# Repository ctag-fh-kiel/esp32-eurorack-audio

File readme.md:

# ESP32 Eurorack Audio Synthesis Module
Hardware for Strämpler

## What it is
Base board (design with KiCad) for using the ESP32 WROVER module in the context of real-time audio applications for eurorack synthesizer setups.

## Errata
CV in 1+2 are -1.5V .. 5.5V

## License
Licensed under CC BY-NC-SA 4.0
https://creativecommons.org/licenses/by-nc-sa/4.0/
(C) Robert Manzke 2019

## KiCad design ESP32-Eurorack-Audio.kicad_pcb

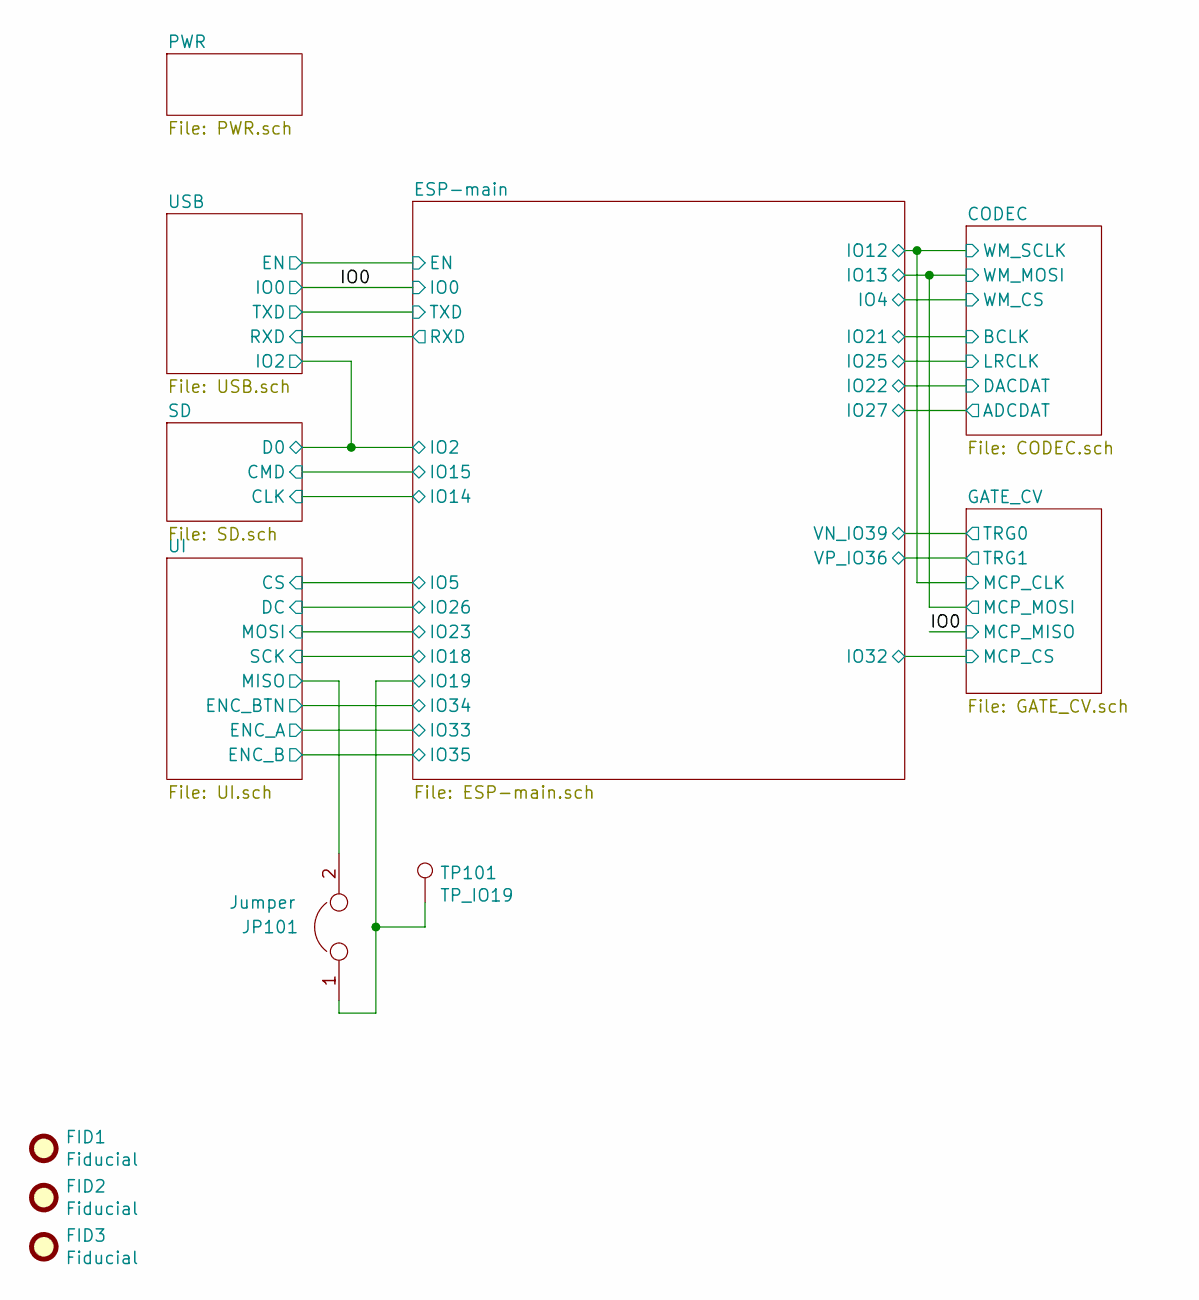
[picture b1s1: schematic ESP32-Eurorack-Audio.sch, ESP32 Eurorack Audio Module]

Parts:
FID1, FID2, FID3: Fiducial; Fiducial_1mm_Mask2mm
JP101: Jumper; SolderJumper-2_P1.3mm_Open_TrianglePad1.0x1.5mm
TP101: TP_IO19; TestPoint_Keystone_5019_Minature

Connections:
/ESP-main/IO19: JP101.1, TP101.1; also elsewhere on the board
/UI/MISO: JP101.2; also elsewhere on the board

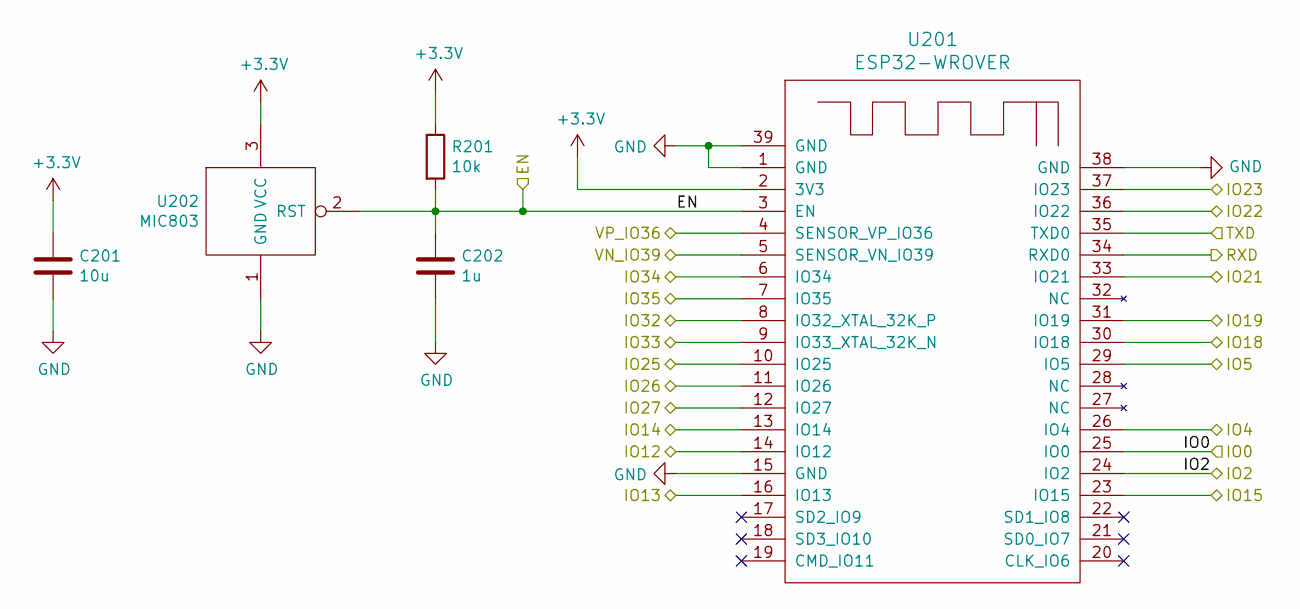
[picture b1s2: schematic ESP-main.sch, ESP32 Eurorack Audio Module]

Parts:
C201: 10u; C_0805_2012Metric
C202: 1u; C_0603_1608Metric
R201: 10k; R_0603_1608Metric
U201: ESP32-WROVER
U202: MIC803; SOT-23

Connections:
/CODEC/ADCDAT: U201.12 (IO27); also elsewhere on the board
/CODEC/BCLK: U201.33 (IO21); also elsewhere on the board
/CODEC/DACDAT: U201.36 (IO22); also elsewhere on the board
/ESP-main/EN: C202.1, R201.2, U201.3 (EN), U202.2 (RST); also elsewhere on the board
/ESP-main/IO4: U201.26 (IO4); also elsewhere on the board
/ESP-main/IO12: U201.14 (IO12); also elsewhere on the board
/ESP-main/IO13: U201.16 (IO13); also elsewhere on the board
/ESP-main/IO18: U201.30 (IO18); also elsewhere on the board
/ESP-main/IO19: U201.31 (IO19); also elsewhere on the board
/ESP-main/IO23: U201.37 (IO23); also elsewhere on the board
/ESP-main/IO25: U201.10 (IO25); also elsewhere on the board
/ESP-main/IO32: U201.8 (IO32_XTAL_32K_P); also elsewhere on the board
/ESP-main/RXD: U201.34 (RXD0); also elsewhere on the board
/ESP-main/TXD: U201.35 (TXD0); also elsewhere on the board
/GATE_CV/TRG0: U201.5 (SENSOR_VN_IO39); also elsewhere on the board
/GATE_CV/TRG1: U201.4 (SENSOR_VP_IO36); also elsewhere on the board
/IO0: U201.25 (IO0); also elsewhere on the board
/SD/CLK: U201.13 (IO14); also elsewhere on the board
/SD/CMD: U201.23 (IO15); also elsewhere on the board
/SD/D0: U201.24 (IO2); also elsewhere on the board
/UI/CS: U201.29 (IO5); also elsewhere on the board
/UI/DC: U201.11 (IO26); also elsewhere on the board
/UI/ENC_A: U201.9 (IO33_XTAL_32K_N); also elsewhere on the board
/UI/ENC_B: U201.7 (IO35); also elsewhere on the board
/UI/ENC_BTN: U201.6 (IO34); also elsewhere on the board
GND: C201.2, C202.2, U201.1 (GND), U201.15 (GND), U201.38 (GND), U201.39 (GND), U202.1 (GND); also elsewhere on the board

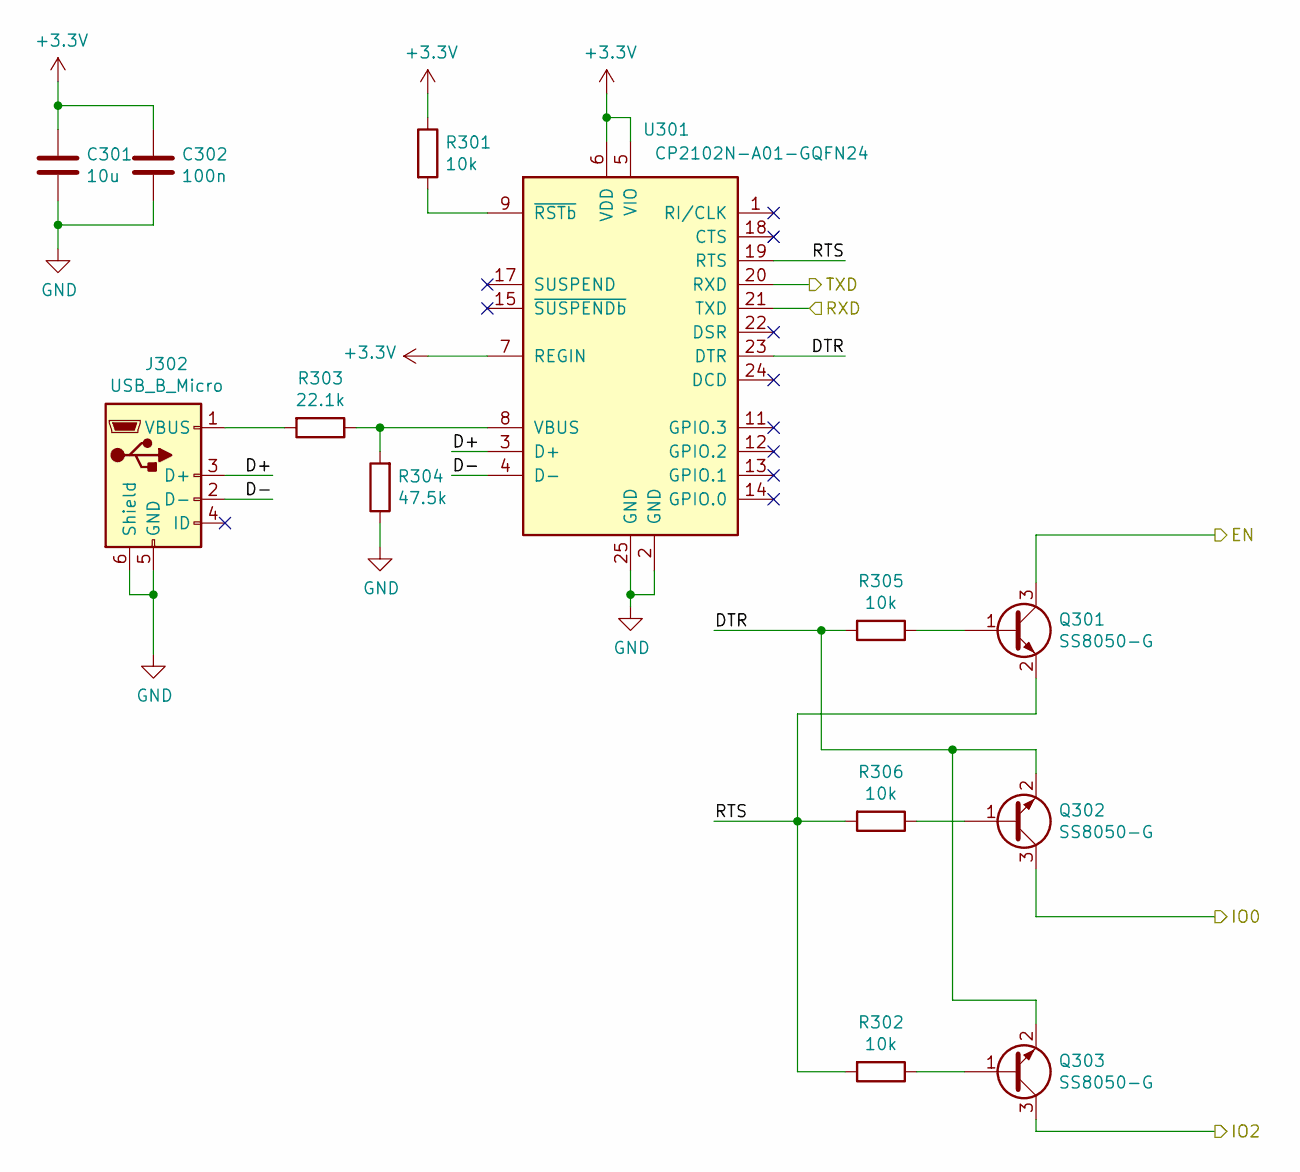
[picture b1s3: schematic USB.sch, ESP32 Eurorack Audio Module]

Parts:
C301: 10u; C_0805_2012Metric
C302: 100n; C_0603_1608Metric
J302: USB_B_Micro; USB_Micro-B_Molex-105017-0001
Q301, Q302, Q303: SS8050-G; SOT-23
R301, R302, R305, R306: 10k; R_0603_1608Metric
R303: 22.1k; R_0603_1608Metric
R304: 47.5k; R_0603_1608Metric
U301: CP2102N-A01-GQFN24; QFN-24-1EP_4x4mm_P0.5mm_EP2.6x2.6mm

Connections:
/ESP-main/EN: Q301.3 (C); also elsewhere on the board
/ESP-main/RXD: U301.21 (TXD); also elsewhere on the board
/ESP-main/TXD: U301.20 (RXD); also elsewhere on the board
/IO0: Q302.3 (C); also elsewhere on the board
/SD/D0: Q303.3 (C); also elsewhere on the board
/USB/D+: J302.3 (D+), U301.3 (D+)
/USB/D-: J302.2 (D-), U301.4 (D-)
/USB/DTR: Q302.2 (E), Q303.2 (E), R305.2, U301.23 (DTR)
/USB/RTS: Q301.2 (E), R302.2, R306.2, U301.19 (RTS)
GND: C301.2, C302.2, J302.5 (GND), J302.6 (Shield), R304.1, U301.2 (GND), U301.25 (GND); also elsewhere on the board
unnamed: J302.1 (VBUS), R303.2
unnamed: Q301.1 (B), R305.1
unnamed: Q302.1 (B), R306.1
unnamed: Q303.1 (B), R302.1
unnamed: R301.2, U301.9 (~RSTb)
unnamed: R303.1, R304.2, U301.8 (VBUS)

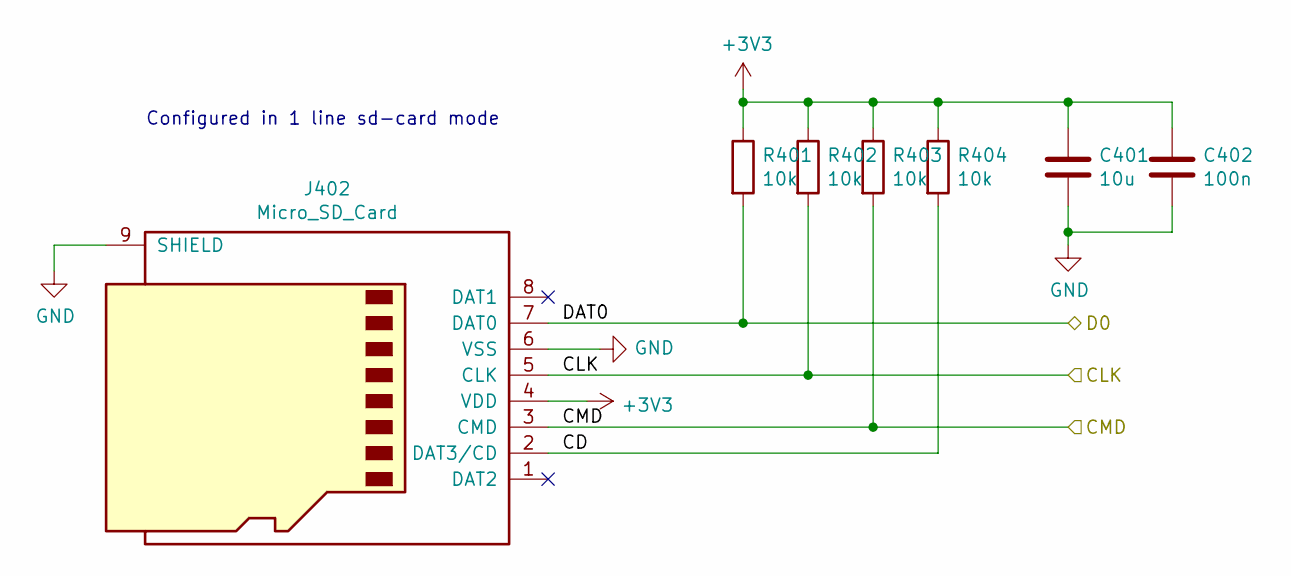
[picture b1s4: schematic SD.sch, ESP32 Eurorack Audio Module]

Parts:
C401: 10u; C_0805_2012Metric
C402: 100n; C_0603_1608Metric
J402: Micro_SD_Card; microSD_HC_Hirose_DM3D-SF
R401, R402, R403, R404: 10k; R_0603_1608Metric

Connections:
/SD/CD: J402.2 (DAT3/CD), R404.2
/SD/CLK: J402.5 (CLK), R402.2; also elsewhere on the board
/SD/CMD: J402.3 (CMD), R403.2; also elsewhere on the board
/SD/D0: J402.7 (DAT0), R401.2; also elsewhere on the board
GND: C401.2, C402.2, J402.6 (VSS), J402.9 (SHIELD); also elsewhere on the board

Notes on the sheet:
Configured in 1 line sd-card mode

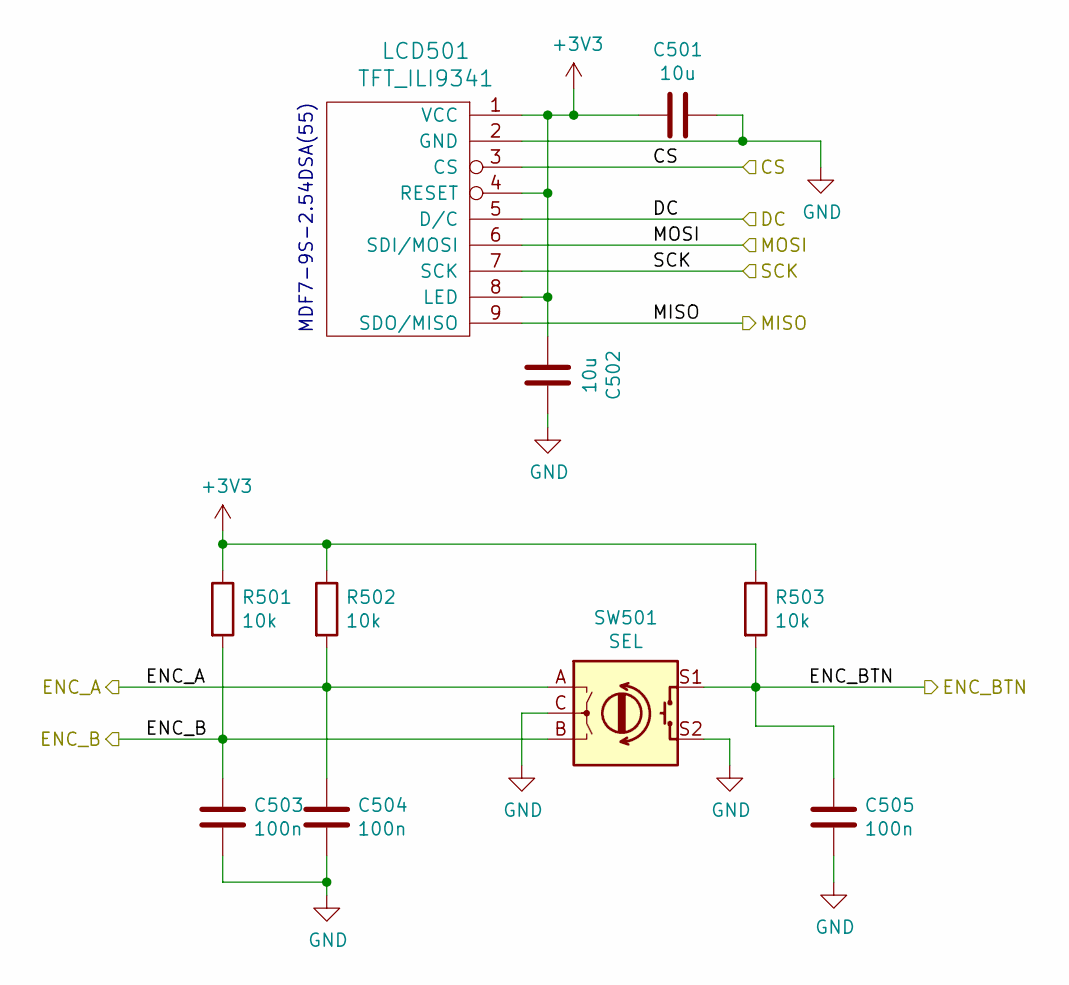
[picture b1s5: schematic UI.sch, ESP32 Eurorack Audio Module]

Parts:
C501, C502: 10u; C_0805_2012Metric
C503, C504, C505: 100n; C_0603_1608Metric
LCD501: TFT_ILI9341; TFT_2.2
R501, R502, R503: 10k; R_0603_1608Metric
SW501: SEL; RotaryEncoder_Alps_EC11E-Switch_Vertical_H20mm

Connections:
/ESP-main/IO18: LCD501.7 (SCK); also elsewhere on the board
/ESP-main/IO23: LCD501.6 (SDI/MOSI); also elsewhere on the board
/UI/CS: LCD501.3 (CS); also elsewhere on the board
/UI/DC: LCD501.5 (D/C); also elsewhere on the board
/UI/ENC_A: C504.2, R502.2, SW501.A; also elsewhere on the board
/UI/ENC_B: C503.2, R501.2, SW501.B; also elsewhere on the board
/UI/ENC_BTN: C505.2, R503.2, SW501.S1; also elsewhere on the board
/UI/MISO: LCD501.9 (SDO/MISO); also elsewhere on the board
GND: C501.1, C502.1, C503.1, C504.1, C505.1, LCD501.2 (GND), SW501.C, SW501.S2; also elsewhere on the board

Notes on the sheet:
MDF7-9S-2.54DSA(55)

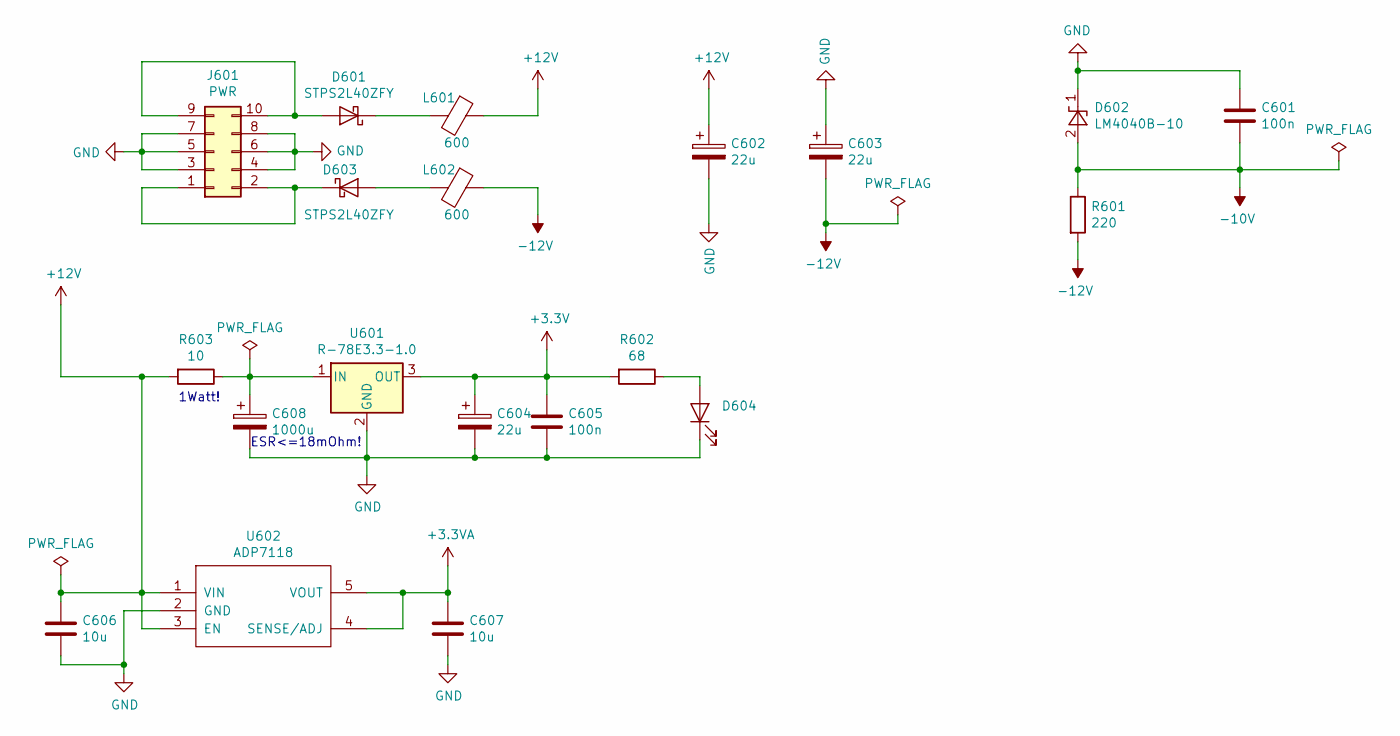
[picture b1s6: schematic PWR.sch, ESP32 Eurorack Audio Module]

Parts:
C601, C605: 100n; C_0603_1608Metric
C602, C603, C604: 22u; CP_EIA-3216-12_Kemet-S
C606: 10u; C_1210_3225Metric
C607: 10u; C_0805_2012Metric
C608: 1000u; CP_Elec_10x12.6
D601, D603: STPS2L40ZFY; D_SOD-123
D602: LM4040B-10; SOT-23
D604: LED_D5.0mm_Clear
J601: PWR; PinHeader_2x05_P2.54mm_Vertical
L601, L602: 600; C_0805_2012Metric
R601: 220; R_0603_1608Metric
R602: 68; R_0805_2012Metric
R603: 10; R_2512_6332Metric
U601: R-78E3.3-1.0; SIP3_11.6x8.5mm
U602: ADP7118; TSOT-23-5

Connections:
+3.3VA: C607.1, U602.4 (SENSE/ADJ), U602.5 (VOUT); also elsewhere on the board
+12V: C602.1, C606.1, L601.1, R603.2, U602.1 (VIN), U602.3 (EN); also elsewhere on the board
-10V: C601.2, D602.2 (A), R601.1; also elsewhere on the board
-12V: C603.2, L602.1, R601.2; also elsewhere on the board
GND: C601.1, C602.2, C603.1, C604.2, C605.2, C606.2, C607.2, C608.2, D602.1 (K), D604.1 (K), J601.3, J601.4, J601.5, J601.6, J601.7, J601.8, U601.2 (GND), U602.2 (GND); also elsewhere on the board
unnamed: C608.1, R603.1, U601.1 (IN)
unnamed: D601.1 (K), L601.2
unnamed: D601.2 (A), J601.9, J601.10
unnamed: D603.1 (K), J601.1, J601.2
unnamed: D603.2 (A), L602.2
unnamed: D604.2 (A), R602.1

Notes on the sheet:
ESR<=18mOhm!
1Watt!

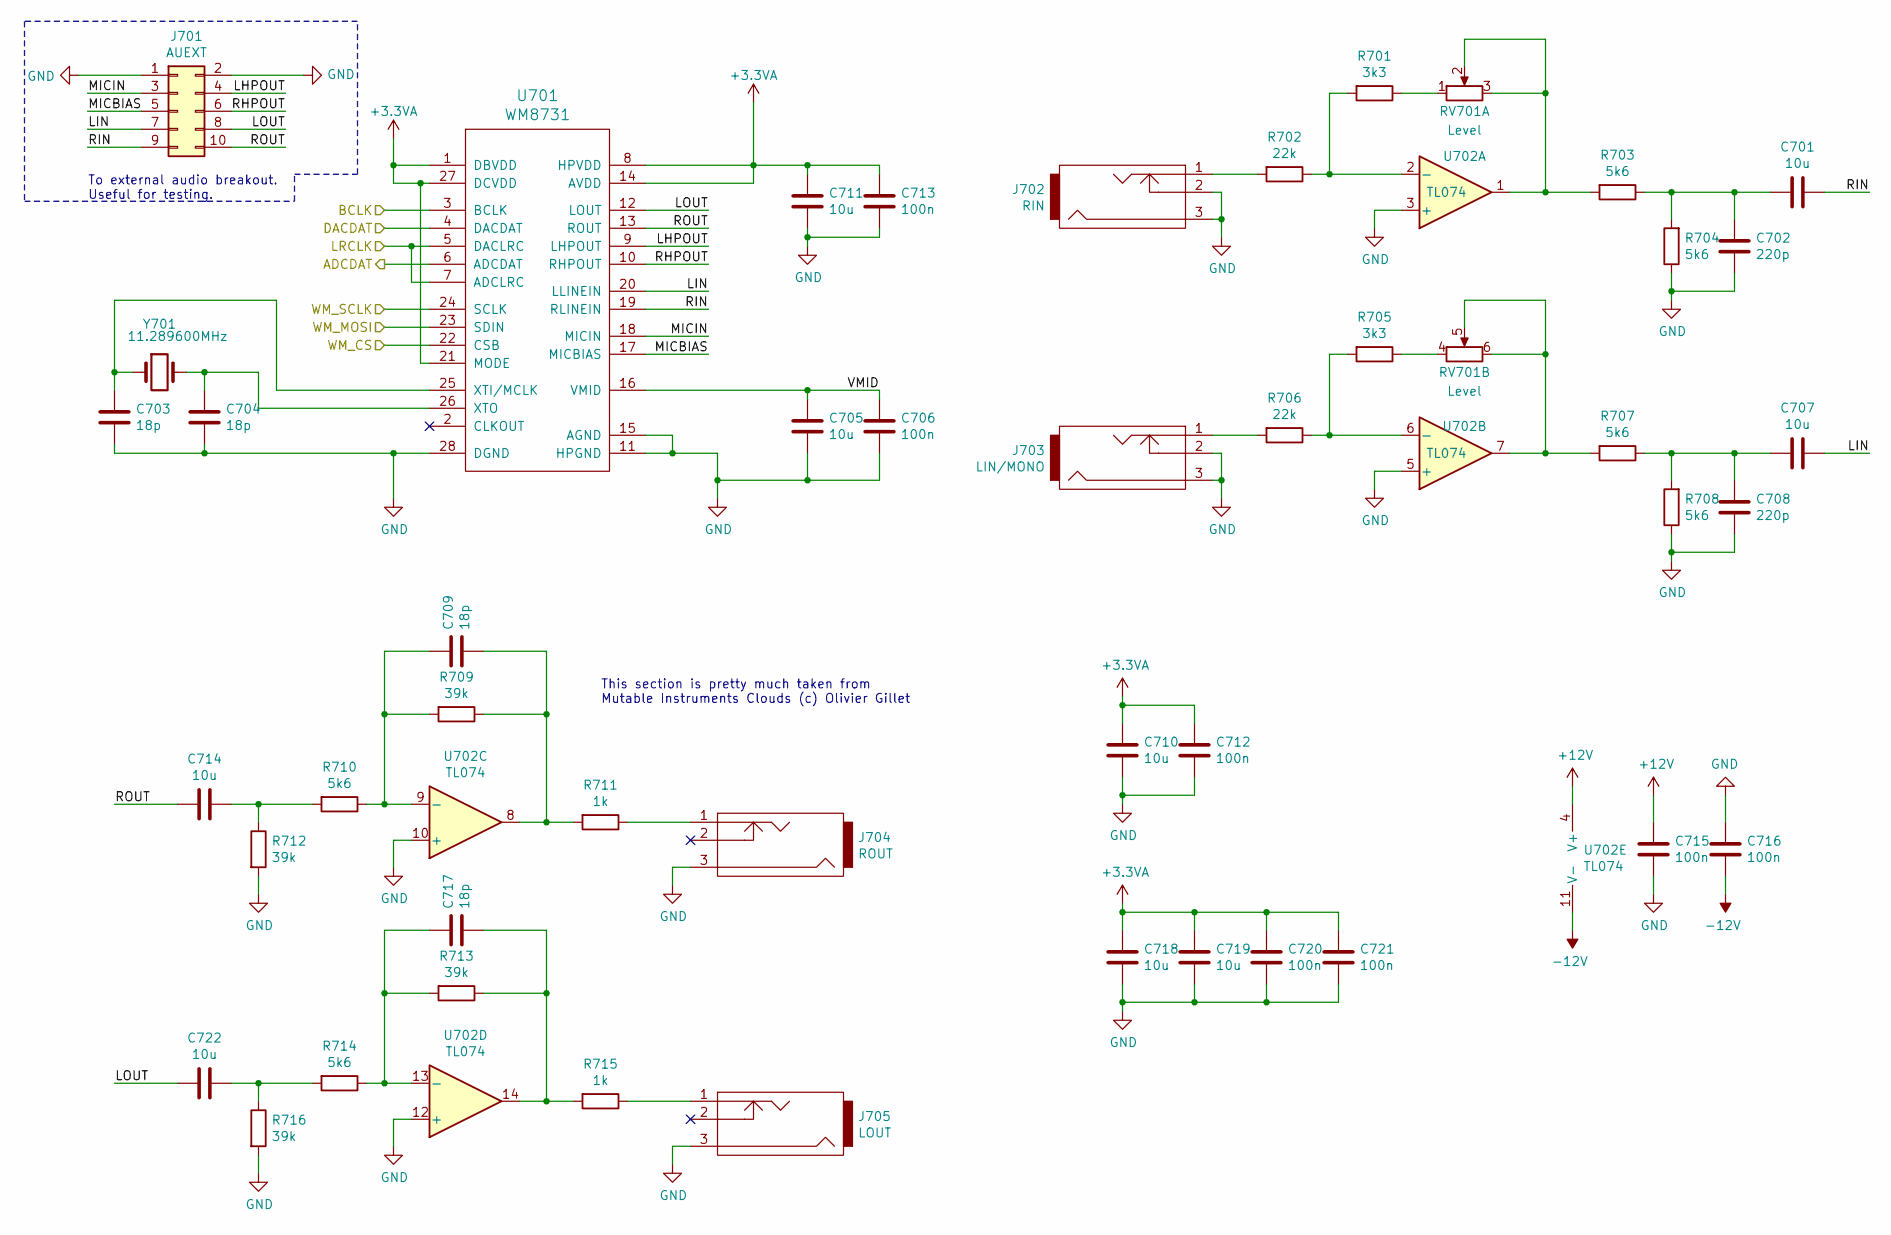
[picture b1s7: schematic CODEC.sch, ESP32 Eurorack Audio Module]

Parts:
C701, C705, C707, C710, C711, C714, C718, C719, C722: 10u; C_0805_2012Metric
C702, C708: 220p; C_0603_1608Metric
C703, C704, C709, C717: 18p; C_0603_1608Metric
C706, C712, C713, C715, C716, C720, C721: 100n; C_0603_1608Metric
J701: AUEXT; PinHeader_2x05_P2.54mm_Vertical_SMD
J702: RIN; THONKICONN
J703: LIN/MONO; THONKICONN
J704: ROUT; THONKICONN
J705: LOUT; THONKICONN
R701, R705: 3k3; R_0603_1608Metric
R702, R706: 22k; R_0603_1608Metric
R703, R704, R707, R708, R710, R714: 5k6; R_0603_1608Metric
R709, R712, R713, R716: 39k; R_0603_1608Metric
R711, R715: 1k; R_0603_1608Metric
RV701: Level; Alpha_9mm_stereo
U701: WM8731; SSOP-28_5.3x10.2mm_P0.65mm
U702: TL074; TSSOP-14_4.4x5mm_P0.65mm
Y701: 11.289600MHz; Crystal_SMD_HC49-SD

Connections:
+3.3VA: C710.1, C711.1, C712.1, C713.1, C718.1, C719.1, C720.1, C721.1, U701.1 (DBVDD), U701.8 (HPVDD), U701.14 (AVDD), U701.21 (MODE), U701.27 (DCVDD); also elsewhere on the board
+12V: C715.1, U702.4 (V+); also elsewhere on the board
-12V: C716.2, U702.11 (V-); also elsewhere on the board
/CODEC/ADCDAT: U701.6 (ADCDAT); also elsewhere on the board
/CODEC/BCLK: U701.3 (BCLK); also elsewhere on the board
/CODEC/DACDAT: U701.4 (DACDAT); also elsewhere on the board
/CODEC/LHPOUT: J701.4, U701.9 (LHPOUT)
/CODEC/LIN: C707.1, J701.7, U701.20 (LLINEIN)
/CODEC/LOUT: C722.2, J701.8, U701.12 (LOUT)
/CODEC/MICBIAS: J701.5, U701.17 (MICBIAS)
/CODEC/MICIN: J701.3, U701.18 (MICIN)
/CODEC/RHPOUT: J701.6, U701.10 (RHPOUT)
/CODEC/RIN: C701.1, J701.9, U701.19 (RLINEIN)
/CODEC/ROUT: C714.2, J701.10, U701.13 (ROUT)
/CODEC/VMID: C705.1, C706.1, U701.16 (VMID)
/ESP-main/IO4: U701.22 (CSB); also elsewhere on the board
/ESP-main/IO12: U701.24 (SCLK); also elsewhere on the board
/ESP-main/IO13: U701.23 (SDIN); also elsewhere on the board
/ESP-main/IO25: U701.5 (DACLRC), U701.7 (ADCLRC); also elsewhere on the board
GND: C702.2, C703.2, C704.2, C705.2, C706.2, C708.2, C710.2, C711.2, C712.2, C713.2, C715.2, C716.1, C718.2, C719.2, C720.2, C721.2, J701.1, J701.2, J702.2, J702.3, J703.2, J703.3, J704.3, J705.3, R704.1, R708.1, R712.2, R716.2, U701.11 (HPGND), U701.15 (AGND), U701.28 (DGND), U702.3 (+), U702.5 (+), U702.10 (+), U702.12 (+); also elsewhere on the board
unnamed: C701.2, C702.1, R703.1, R704.2
unnamed: C703.1, U701.25 (XTI/MCLK), Y701.1
unnamed: C704.1, U701.26 (XTO), Y701.2
unnamed: C707.2, C708.1, R707.1, R708.2
unnamed: C709.1, R709.2, R710.1, U702.9 (-)
unnamed: C709.2, R709.1, R711.2, U702.8
unnamed: C714.1, R710.2, R712.1
unnamed: C717.1, R713.2, R714.1, U702.13 (-)
unnamed: C717.2, R713.1, R715.2, U702.14
unnamed: C722.1, R714.2, R716.1
unnamed: J702.1, R702.2
unnamed: J703.1, R706.2
unnamed: J704.1, R711.1
unnamed: J705.1, R715.1
unnamed: R701.1, RV701.1
unnamed: R701.2, R702.1, U702.2 (-)
unnamed: R703.2, RV701.2, RV701.3, U702.1
unnamed: R705.1, RV701.4
unnamed: R705.2, R706.1, U702.6 (-)
unnamed: R707.2, RV701.5, RV701.6, U702.7

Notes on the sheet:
This section is pretty much taken from Mutable Instruments Clouds (c) Olivier Gillet
To external audio breakout. Useful for testing.

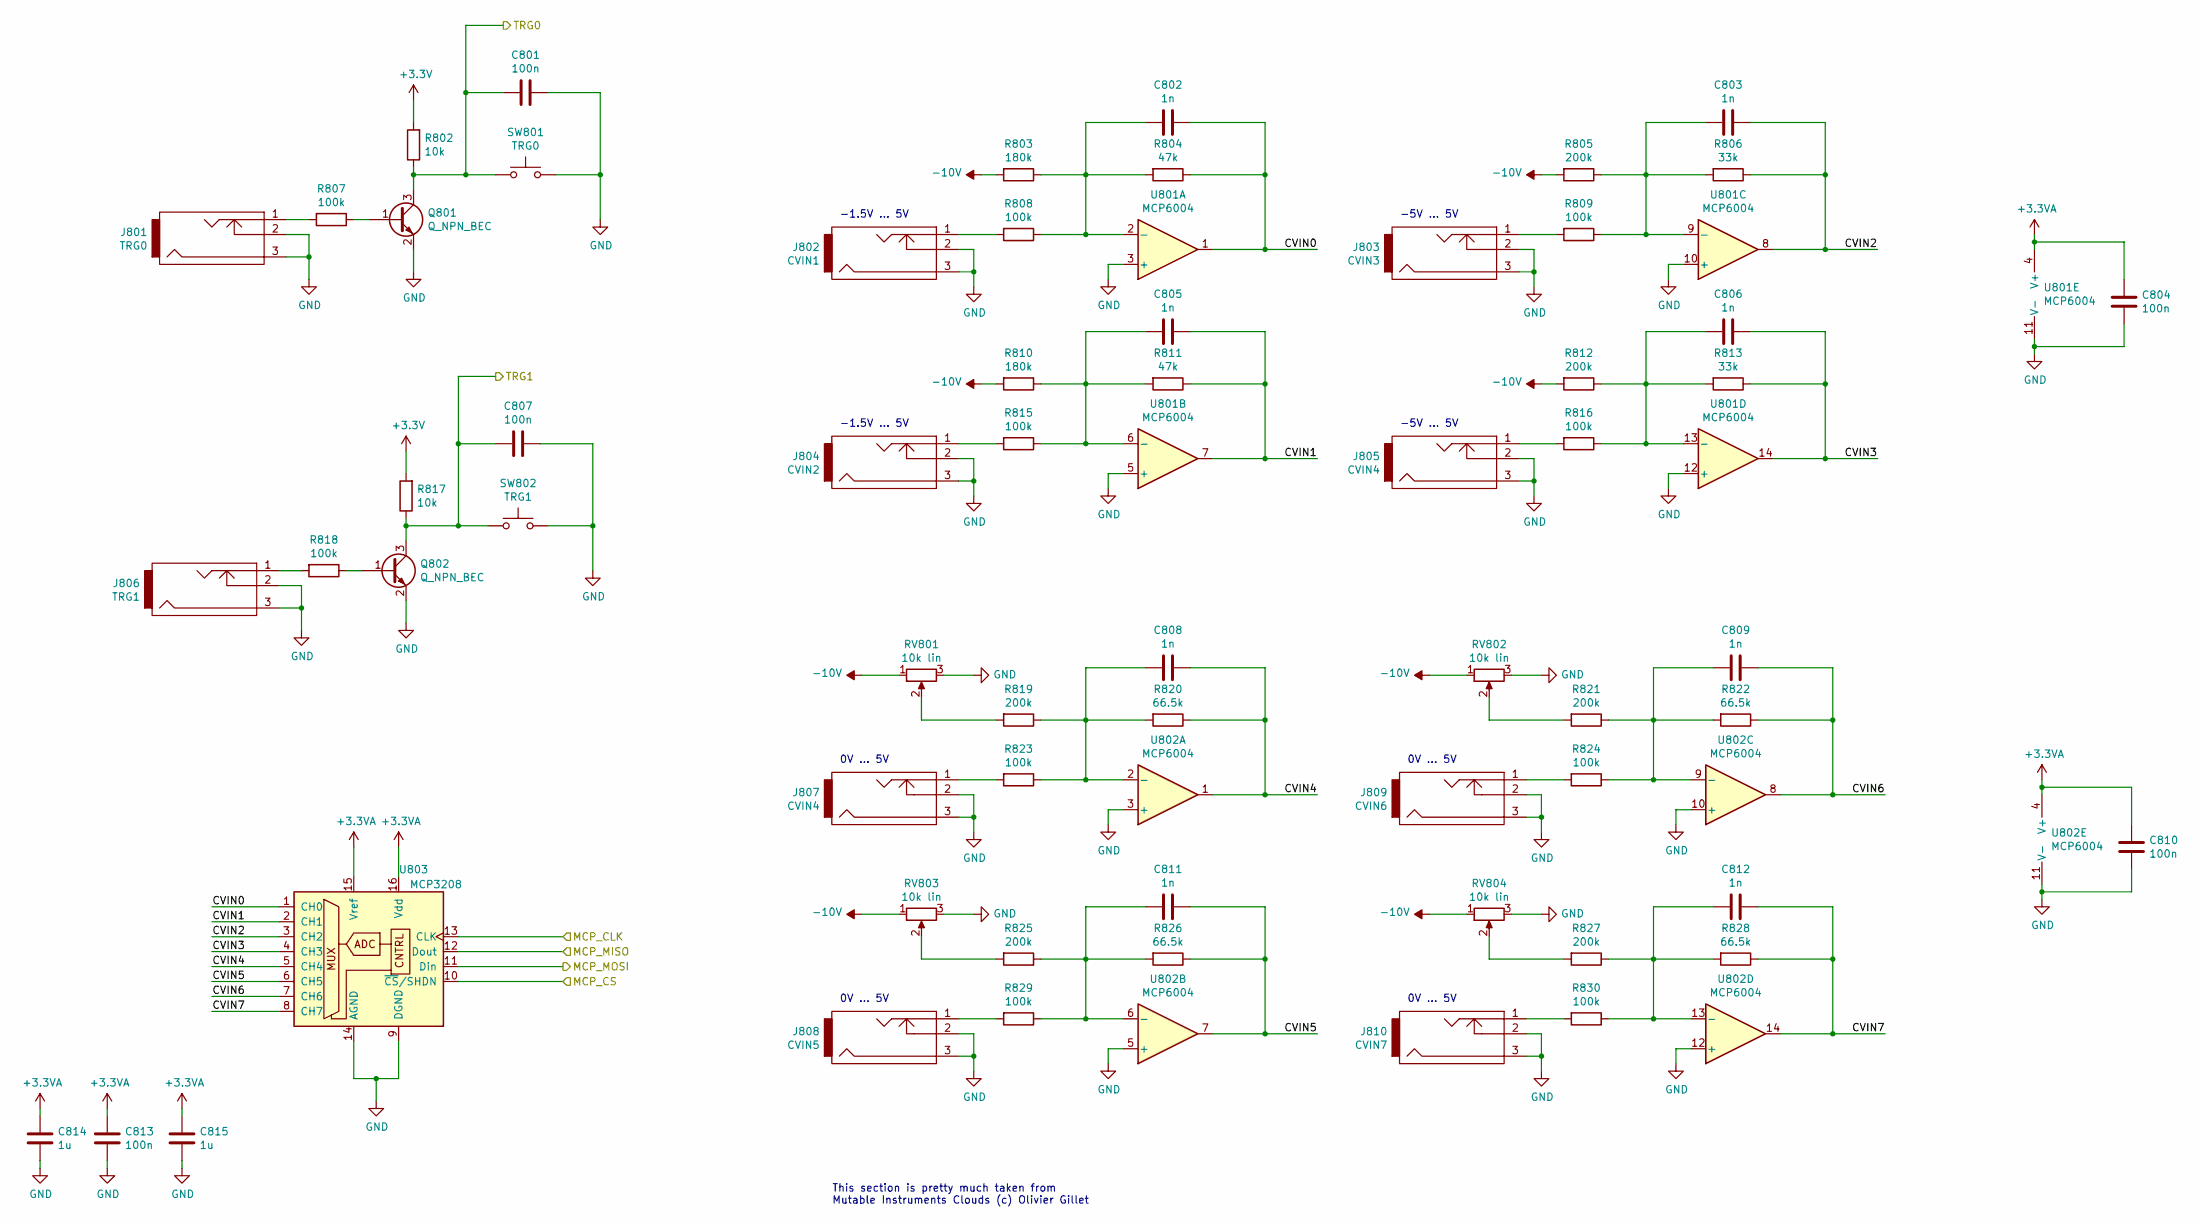
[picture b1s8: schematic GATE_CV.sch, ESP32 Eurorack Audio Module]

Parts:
C801, C804, C807, C810, C813: 100n; C_0603_1608Metric
C802, C803, C805, C806, C808, C809, C811, C812: 1n; C_0603_1608Metric
C814, C815: 1u; C_0603_1608Metric
J801: TRG0; THONKICONN
J802: CVIN1; THONKICONN
J803: CVIN3; THONKICONN
J804: CVIN2; THONKICONN
J805, J807: CVIN4; THONKICONN
J806: TRG1; THONKICONN
J808: CVIN5; THONKICONN
J809: CVIN6; THONKICONN
J810: CVIN7; THONKICONN
Q801, Q802: Q_NPN_BEC; SOT-23
R802, R817: 10k; R_0603_1608Metric
R803, R810: 180k; R_0603_1608Metric
R804, R811: 47k; R_0603_1608Metric
R805, R812, R819, R821, R825, R827: 200k; R_0603_1608Metric
R806, R813: 33k; R_0603_1608Metric
R807, R808, R809, R815, R816, R818, R823, R824, R829, R830: 100k; R_0603_1608Metric
R820, R822, R826, R828: 66.5k; R_0603_1608Metric
RV801, RV802, RV803, RV804: 10k lin; Alpha_9mm
SW801: TRG0; SW_6425
SW802: TRG1; SW_6425
U801, U802: MCP6004; TSSOP-14_4.4x5mm_P0.65mm
U803: MCP3208; SOIC-16_3.9x9.9mm_P1.27mm

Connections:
+3.3VA: C804.1, C810.1, C813.1, C814.1, C815.1, U801.4 (V+), U802.4 (V+), U803.15 (Vref), U803.16 (Vdd); also elsewhere on the board
-10V: R803.2, R805.2, R810.2, R812.2, RV801.1, RV802.1, RV803.1, RV804.1; also elsewhere on the board
/ESP-main/IO12: U803.13 (CLK); also elsewhere on the board
/ESP-main/IO13: U803.11 (Din); also elsewhere on the board
/ESP-main/IO32: U803.10 (~CS~/SHDN); also elsewhere on the board
/GATE_CV/CVIN0: C802.1, R804.1, U801.1, U803.1 (CH0)
/GATE_CV/CVIN1: C805.1, R811.1, U801.7, U803.2 (CH1)
/GATE_CV/CVIN2: C803.1, R806.1, U801.8, U803.3 (CH2)
/GATE_CV/CVIN3: C806.1, R813.1, U801.14, U803.4 (CH3)
/GATE_CV/CVIN4: C808.1, R820.1, U802.1, U803.5 (CH4)
/GATE_CV/CVIN5: C811.1, R826.1, U802.7, U803.6 (CH5)
/GATE_CV/CVIN6: C809.1, R822.1, U802.8, U803.7 (CH6)
/GATE_CV/CVIN7: C812.1, R828.1, U802.14, U803.8 (CH7)
/GATE_CV/TRG0: C801.2, Q801.3 (C), R802.1, SW801.1; also elsewhere on the board
/GATE_CV/TRG1: C807.2, Q802.3 (C), R817.1, SW802.1; also elsewhere on the board
/IO0: U803.12 (Dout); also elsewhere on the board
GND: C801.1, C804.2, C807.1, C810.2, C813.2, C814.2, C815.2, J801.2, J801.3, J802.2, J802.3, J803.2, J803.3, J804.2, J804.3, J805.2, J805.3, J806.2, J806.3, J807.2, J807.3, J808.2, J808.3, J809.2, J809.3, J810.2, J810.3, Q801.2 (E), Q802.2 (E), RV801.3, RV802.3, RV803.3, RV804.3, SW801.2, SW802.2, U801.3 (+), U801.5 (+), U801.10 (+), U801.11 (V-), U801.12 (+), U802.3 (+), U802.5 (+), U802.10 (+), U802.11 (V-), U802.12 (+), U803.9 (DGND), U803.14 (AGND); also elsewhere on the board
unnamed: C802.2, R803.1, R804.2, R808.1, U801.2 (-)
unnamed: C803.2, R805.1, R806.2, R809.1, U801.9 (-)
unnamed: C805.2, R810.1, R811.2, R815.1, U801.6 (-)
unnamed: C806.2, R812.1, R813.2, R816.1, U801.13 (-)
unnamed: C808.2, R819.1, R820.2, R823.1, U802.2 (-)
unnamed: C809.2, R821.1, R822.2, R824.1, U802.9 (-)
unnamed: C811.2, R825.1, R826.2, R829.1, U802.6 (-)
unnamed: C812.2, R827.1, R828.2, R830.1, U802.13 (-)
unnamed: J801.1, R807.2
unnamed: J802.1, R808.2
unnamed: J803.1, R809.2
unnamed: J804.1, R815.2
unnamed: J805.1, R816.2
unnamed: J806.1, R818.2
unnamed: J807.1, R823.2
unnamed: J808.1, R829.2
unnamed: J809.1, R824.2
unnamed: J810.1, R830.2
unnamed: Q801.1 (B), R807.1
unnamed: Q802.1 (B), R818.1
unnamed: R819.2, RV801.2
unnamed: R821.2, RV802.2
unnamed: R825.2, RV803.2
unnamed: R827.2, RV804.2

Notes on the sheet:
-1.5V ... 5V
-5V ... 5V
0V ... 5V
This section is pretty much taken from Mutable Instruments Clouds (c) Olivier Gillet

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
